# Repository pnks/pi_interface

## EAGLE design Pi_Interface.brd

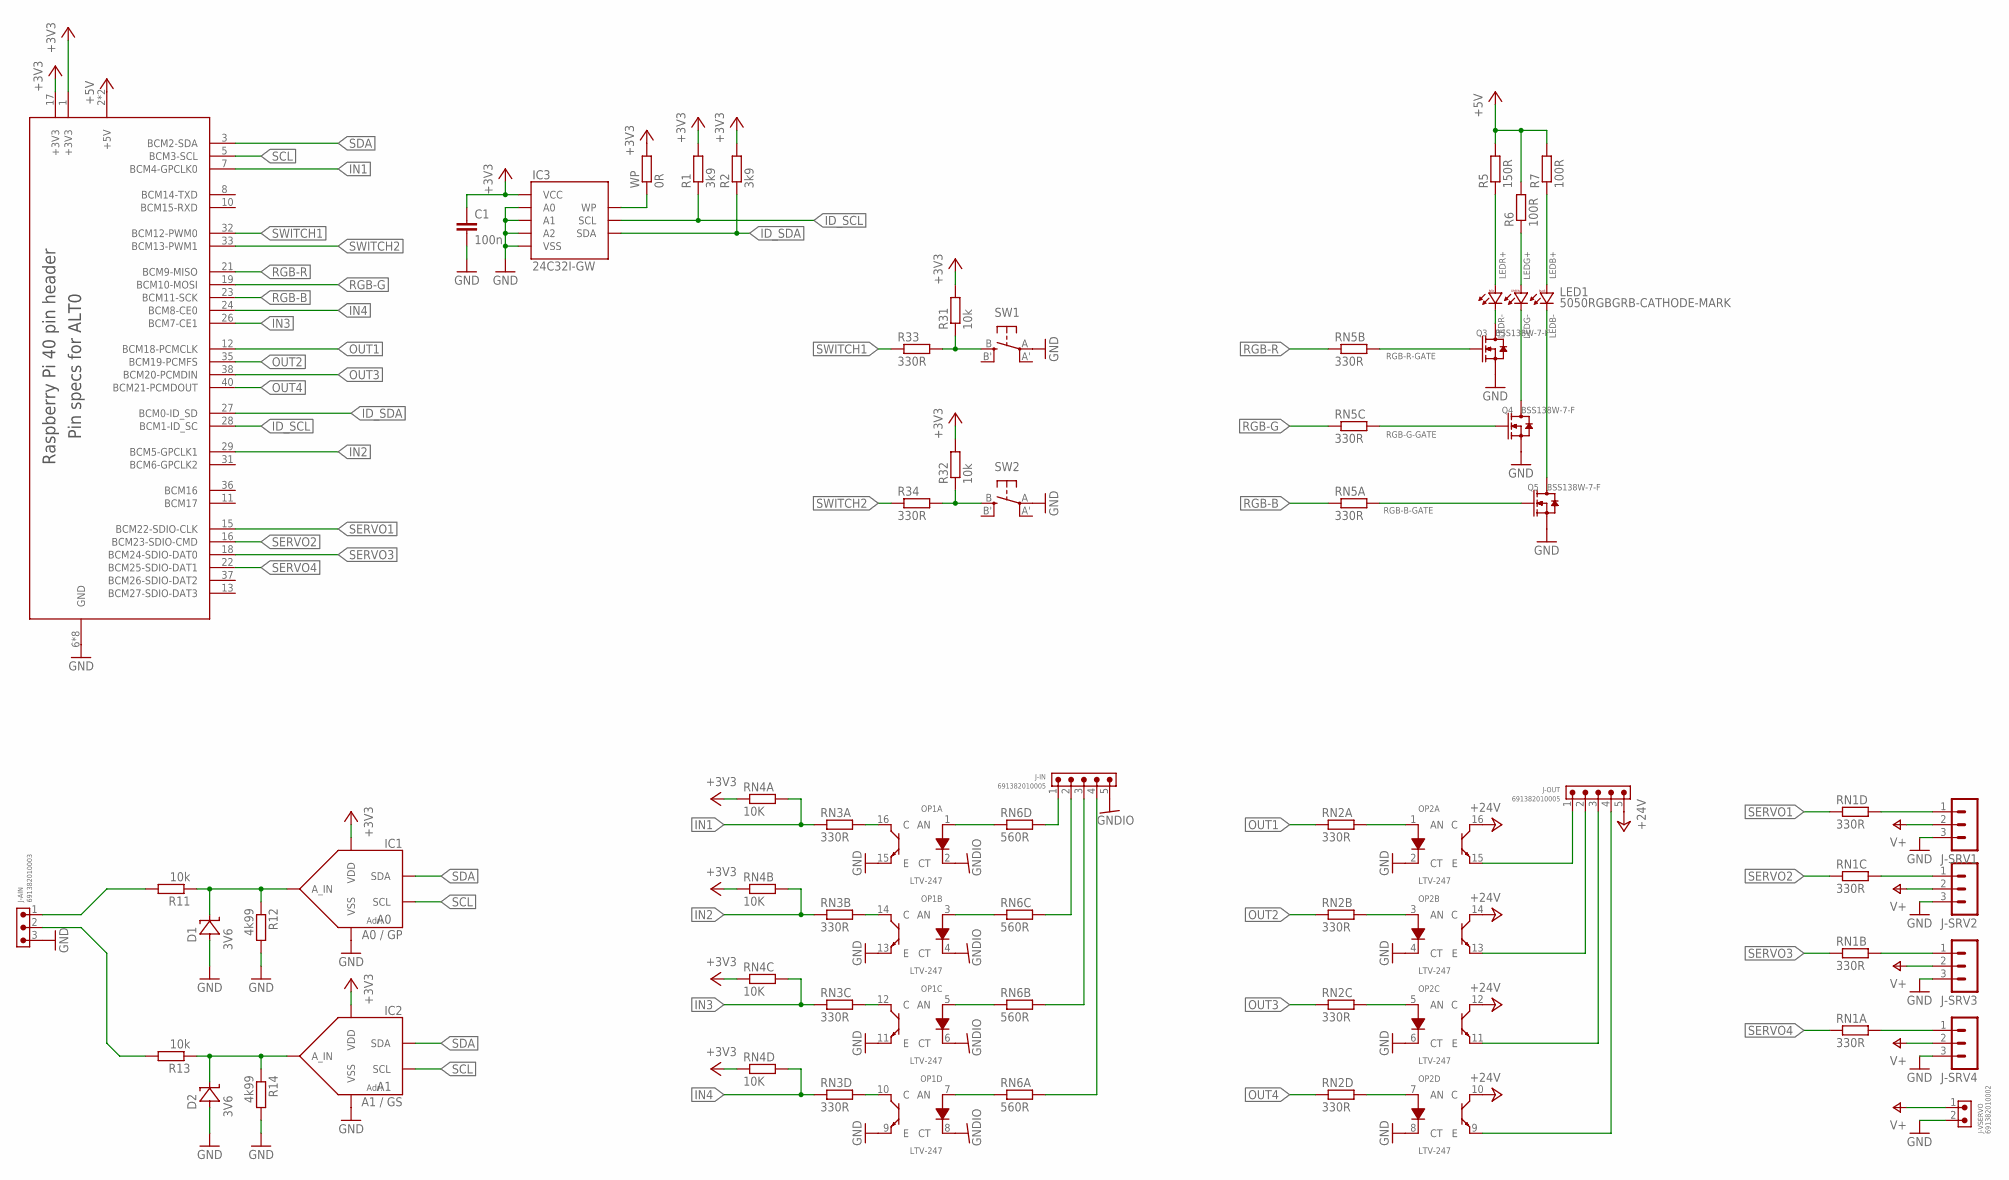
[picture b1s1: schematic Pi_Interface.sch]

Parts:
C1: 100n; C0603
D1, D2: 3V6; SOD3716X115N
IC1: A0 / GP; SOT95P280X145-5N
IC2: A1 / GS; SOT95P280X145-5N
IC3: 24C32I-GW; SOIC127P600X175-8N
J3: RASPI-40HAT; FE20-2
J-AIN: 691382010003
J-IN: 691382010005
J-OUT: 691382010005
J-SRV1, J-SRV2, J-SRV3, J-SRV4: MA03-1
J-VSERVO: 691382010002
LED1: 5050RGBGRB-CATHODE-MARK; CATH_MARK_5050_PLCC6
OP1, OP2: LTV-247; SOIC127P675X220-16N
Q3, Q4, Q5: BSS138W-7-F; SOT-23
R1, R2: 3k9; R0603
R5: 150R; R0603
R6, R7: 100R; R0603
R11, R13, R31, R32: 10k; R0603
R12, R14: 4k99; R0603
R33, R34: 330R; R0603
RN1, RN2, RN5: 330R; RESCAV80P315X160X60-8N
RN3: 330R; RESCAXS80P315X160X60-8N
RN4: 10K; RESCAXS80P315X160X60-8N
RN6: 560R; RESCAXS80P315X160X60-8N
SW1, SW2: SPST_TACT-PT645; PT645-SMT
WP: 0R; R0603

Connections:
+3V3: C1.1, IC1.1 (VDD), IC2.1 (VDD), IC3.8 (VCC), J3.1 (+3V3), J3.17 (+3V3), R1.2, R2.2, R31.2, R32.2, RN4.1, RN4.2 (1), RN4.3 (1), RN4.4 (1), WP.2
+5V: J3.2 (+5V), J3.4 (+5V), R5.2, R6.2, R7.2
+24V: J-OUT.5, OP2.10 (C), OP2.12 (C), OP2.14 (C), OP2.16 (C)
AIN1: J-AIN.1, R11.2
AIN2: J-AIN.2, R13.2
GND: C1.2, D1.2 (A), D2.2 (A), IC1.2 (VSS), IC2.2 (VSS), IC3.1 (A0), IC3.2 (A1), IC3.3 (A2), IC3.4 (VSS), J3.6 (GND), J3.9 (GND), J3.14 (GND), J3.20 (GND), J3.25 (GND), J3.30 (GND), J3.34 (GND), J3.39 (GND), J-AIN.3, J-SRV1.3, J-SRV2.3, J-SRV3.3, J-SRV4.3, J-VSERVO.2, OP1.9 (E), OP1.11 (E), OP1.13 (E), OP1.15 (E), OP2.2 (CT), OP2.4 (CT), OP2.6 (CT), OP2.8 (CT), Q3.2 (S), Q4.2 (S), Q5.2 (S), R12.2, R14.2, SW1.A, SW2.A
GNDIO: J-IN.5, OP1.2 (CT), OP1.4 (CT), OP1.6 (CT), OP1.8 (CT)
ID_SCL: IC3.6 (SCL), J3.28 (BCM1-ID_SC), R1.1
ID_SDA: IC3.5 (SDA), J3.27 (BCM0-ID_SD), R2.1
IN1: J3.7 (BCM4-GPCLK0), RN3.1, RN4.8 (2)
IN2: J3.29 (BCM5-GPCLK1), RN3.2 (1), RN4.7 (2)
IN3: J3.26 (BCM7-CE1), RN3.3 (1), RN4.6 (2)
IN4: J3.24 (BCM8-CE0), RN3.4 (1), RN4.5 (2)
LEDB+: LED1.3 (B+), R7.1
LEDB-: LED1.4 (B-), Q5.3 (D)
LEDG+: LED1.1 (G+), R6.1
LEDG-: LED1.6 (G-), Q4.3 (D)
LEDR+: LED1.2 (R+), R5.1
LEDR-: LED1.5 (R-), Q3.3 (D)
unnamed: J-SRV1.1, RN1.5 (2)
unnamed: J-SRV2.1, RN1.6 (2)
unnamed: J-SRV3.1, RN1.7 (2)
unnamed: J-SRV4.1, RN1.8 (2)
unnamed: D1.1 (C), IC1.3 (A_IN), R11.1, R12.1
unnamed: D2.1 (C), IC2.3 (A_IN), R13.1, R14.1
unnamed: J-OUT.1, OP2.15 (E)
unnamed: J-OUT.2, OP2.13 (E)
unnamed: J-OUT.3, OP2.11 (E)
unnamed: J-OUT.4, OP2.9 (E)
unnamed: OP2.1 (AN), RN2.8 (2)
unnamed: OP2.3 (AN), RN2.7 (2)
unnamed: OP2.5 (AN), RN2.6 (2)
unnamed: OP2.7 (AN), RN2.5 (2)
unnamed: OP1.1 (AN), RN6.4 (1)
unnamed: OP1.3 (AN), RN6.3 (1)
unnamed: OP1.5 (AN), RN6.2 (1)
unnamed: OP1.7 (AN), RN6.1
unnamed: J-IN.1, RN6.5 (2)
unnamed: J-IN.2, RN6.6 (2)
unnamed: J-IN.3, RN6.7 (2)
unnamed: J-IN.4, RN6.8 (2)
unnamed: OP1.10 (C), RN3.5 (2)
unnamed: R32.1, R34.2, SW2.B (S)
unnamed: OP1.12 (C), RN3.6 (2)
unnamed: OP1.14 (C), RN3.7 (2)
unnamed: OP1.16 (C), RN3.8 (2)
unnamed: R31.1, R33.2, SW1.B (S)
OUT1: J3.12 (BCM18-PCMCLK), RN2.1
OUT2: J3.35 (BCM19-PCMFS), RN2.2 (1)
OUT3: J3.38 (BCM20-PCMDIN), RN2.3 (1)
OUT4: J3.40 (BCM21-PCMDOUT), RN2.4 (1)
RGB-B: J3.23 (BCM11-SCK), RN5.1
RGB-B-GATE: Q5.1 (G), RN5.8 (2)
RGB-G: J3.19 (BCM10-MOSI), RN5.3 (1)
RGB-G-GATE: Q4.1 (G), RN5.6 (2)
RGB-R: J3.21 (BCM9-MISO), RN5.2 (1)
RGB-R-GATE: Q3.1 (G), RN5.7 (2)
SCL: IC1.5 (SCL), IC2.5 (SCL), J3.5 (BCM3-SCL)
SDA: IC1.4 (SDA), IC2.4 (SDA), J3.3 (BCM2-SDA)
SERVO1: J3.15 (BCM22-SDIO-CLK), RN1.4 (1)
SERVO2: J3.16 (BCM23-SDIO-CMD), RN1.3 (1)
SERVO3: J3.18 (BCM24-SDIO-DAT0), RN1.2 (1)
SERVO4: J3.22 (BCM25-SDIO-DAT1), RN1.1
SWITCH1: J3.32 (BCM12-PWM0), R33.1
SWITCH2: J3.33 (BCM13-PWM1), R34.1
V+: J-SRV1.2, J-SRV2.2, J-SRV3.2, J-SRV4.2, J-VSERVO.1
WP: IC3.7 (WP), WP.1

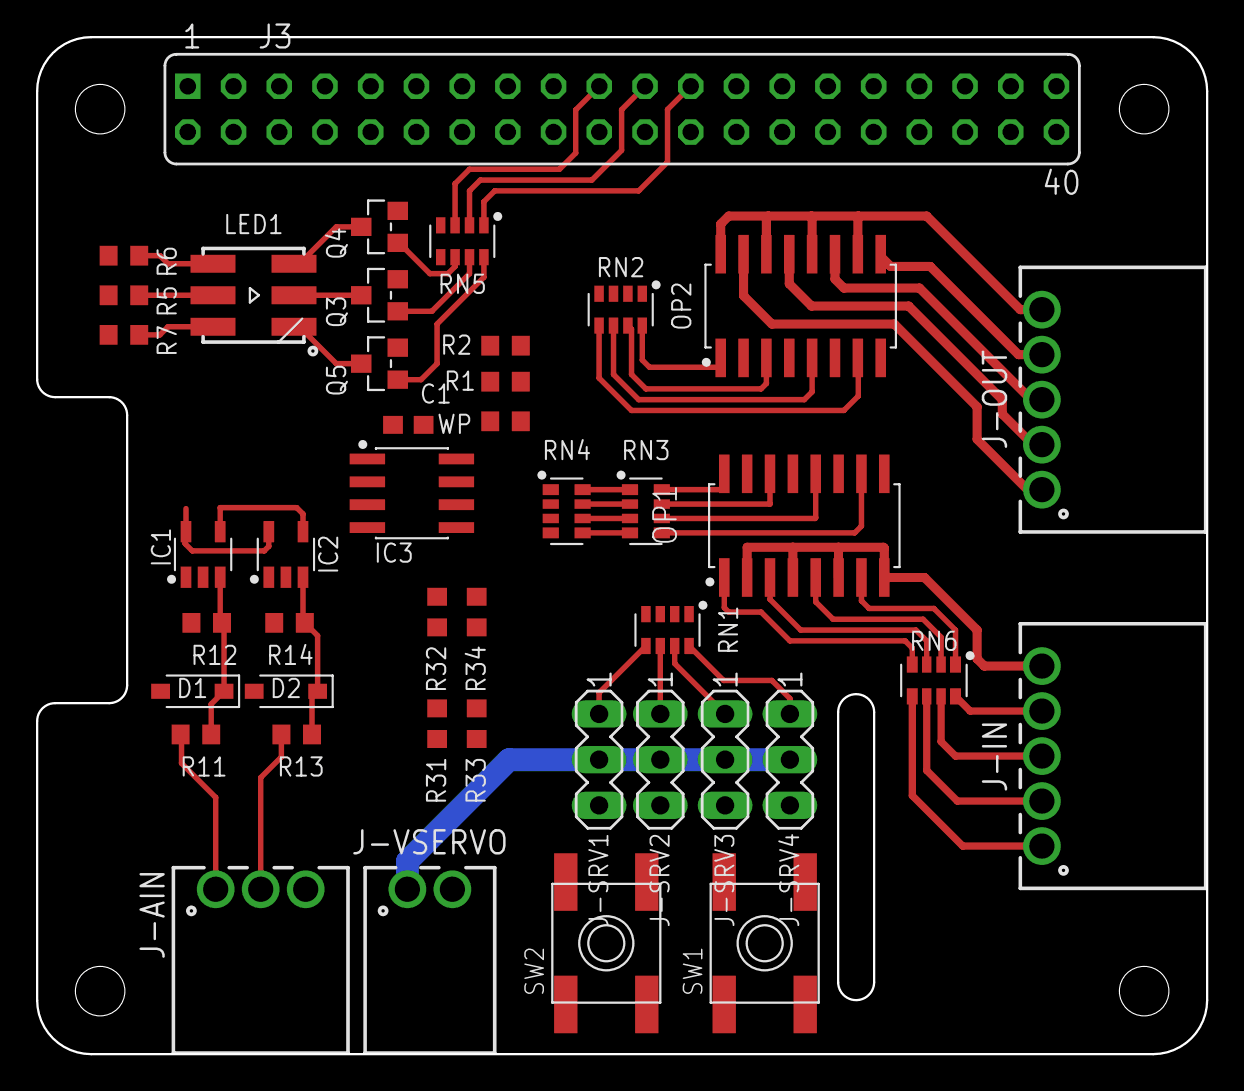
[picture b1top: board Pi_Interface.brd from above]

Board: 2 copper layers, 65.0 x 56.5 mm, 43 parts (0 on the bottom side), 67 nets.

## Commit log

2021-10-11 Initial Project
2021-10-11 Schematic base added
2021-10-11 Added GitIgnore
2021-10-12 Wired up opto-isolators
2021-10-12 Added 1206 resistor networks to minimize component count on board
2021-10-13 Changed Layout, added EEPROM
2021-10-15 Amended calculation

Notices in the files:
parts and their libraries:
Wurth_Connectors_WR-TBL Pluggable Connec: Copyright: Würth Elektronik
